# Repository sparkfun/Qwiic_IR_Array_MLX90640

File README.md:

Qwiic IR Array (MLX90640)
==================

[*Qwiic IR Array (SEN-14843)*](https://www.sparkfun.com/products/14843)
[*Qwiic IR Array (SEN-14844)*](https://www.sparkfun.com/products/14843)

The MLX90640 contains a 32x24 array of thermopile sensors creating, in essence, a low resolution thermal imaging camera.

Repository Contents
-------------------
* **/Documentation** - Datasheets. 
* **/Firmware** - Examples to use the MLX90640 with a microcontroller.
* **/Hardware** - All Eagle design files (.brd, .sch). 
* **/Production** - Various test jigs and large panel layouts used for production.

Documentation
--------------
* **[Library](https://github.com/sparkfun/SparkFun_MLX90640_Arduino_Example)** - Arduino library for the Qwiic IR Array.
* **[Hookup Guide](https://learn.sparkfun.com/tutorials/qwiic-ir-array-mlx90640-hookup-guide)** - Basic hookup guide for the Qwiic IR Array.

Product Versions
----------------
* [SEN-14843](https://www.sparkfun.com/products/14843)- SparkFun 55 degree FOV
* [SEN-14844](https://www.sparkfun.com/products/14844)- SparkFun 110 degree FOV
* [SPX-14768](https://www.sparkfun.com/products/14768)- SparkX version

License Information
-------------------

The hardware is released under [Creative Commons ShareAlike 4.0 International](https://creativecommons.org/licenses/by-sa/4.0/).
The code is beerware; if you see me (or any other SparkFun employee) at the local, and you've found our code helpful, please buy us a round!

Distributed as-is; no warranty is given.

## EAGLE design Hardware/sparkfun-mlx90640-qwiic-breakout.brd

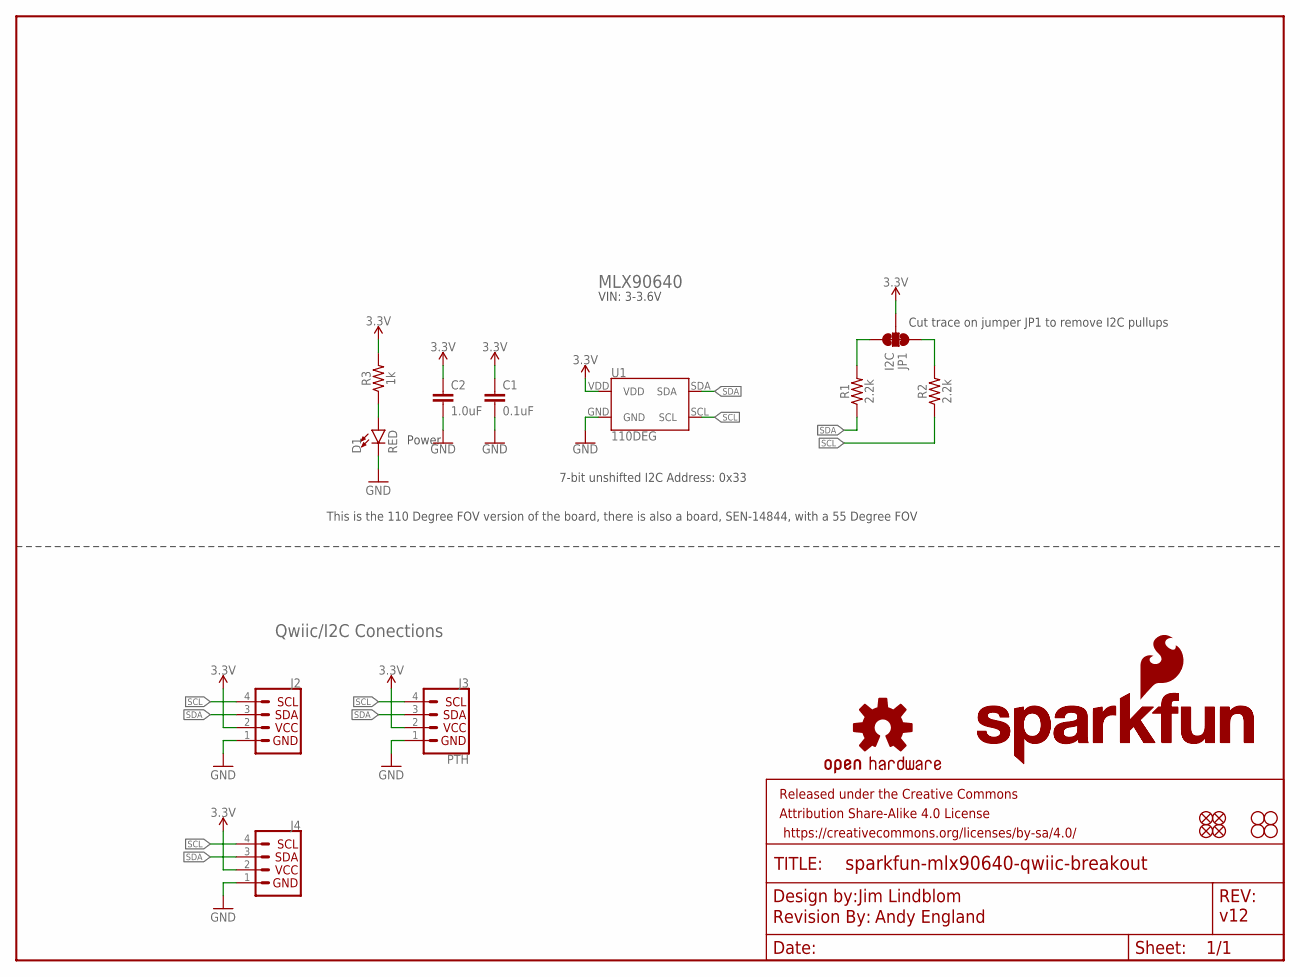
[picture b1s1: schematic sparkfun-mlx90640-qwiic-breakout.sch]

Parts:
C1: 0.1uF; 0603
C2: 1.0uF; 0603
D1: RED; LED-0603
FRAME1: FRAME-LETTER; CREATIVE_COMMONS
J2, J4: QWIIC_CONNECTORJS-1MM; JST04_1MM_RA
J3: PTH; 1X04_NO_SILK
JP1: I2C; SMT-JUMPER_3_2-NC_TRACE_NO-SILK
JP2, JP5, JP6, JP7: FIDUCIALUFIDUCIAL; MICRO-FIDUCIAL
JP3, JP4, JP8, JP9: STAND-OFF
LOGO1: OSHW-LOGOMINI; OSHW-LOGO-MINI
LOGO2: SFE_LOGO_NAME_FLAME.1_INCH; SFE_LOGO_NAME_FLAME_.1
LOGO3: SFE_LOGO_NAME.1_INCH; SFE_LOGO_NAME_.1
LOGO4: REVISION
R1, R2: 2.2k; 0603
R3: 1k; 0603
U1: 110DEG; MLX90540_MLX90640

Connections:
3.3V: C1.1, C2.1, J2.2, J3.2 (VCC), J4.2, JP1.2, R3.2, U1.VDD
GND: C1.2, C2.2, D1.C, J2.1, J3.1 (GND), J4.1, U1.GND
unnamed: JP1.3, R1.2
unnamed: JP1.1, R2.2
unnamed: D1.A, R3.1
SCL: J2.4, J3.4 (SCL), J4.4, R2.1, U1.SCL
SDA: J2.3, J3.3 (SDA), J4.3, R1.1, U1.SDA

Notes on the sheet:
Power
Jim Lindblom
7-bit unshifted I2C Address: 0x33
v12
Andy England
MLX90640
Qwiic/I2C Conections
VIN: 3-3.6V
This is the 110 Degree FOV version of the board, there is also a board, SEN-14844, with a 55 Degree FOV
Cut trace on jumper JP1 to remove I2C pullups

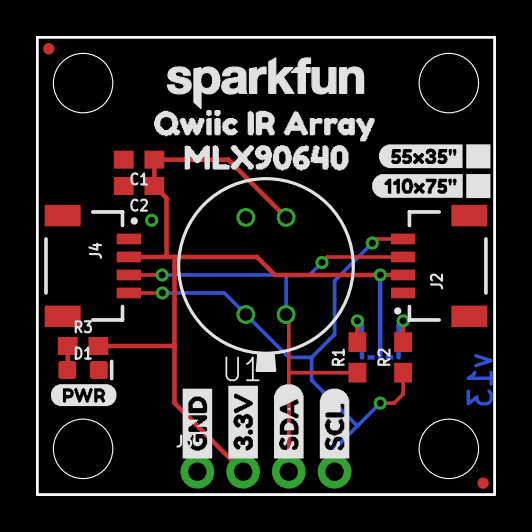
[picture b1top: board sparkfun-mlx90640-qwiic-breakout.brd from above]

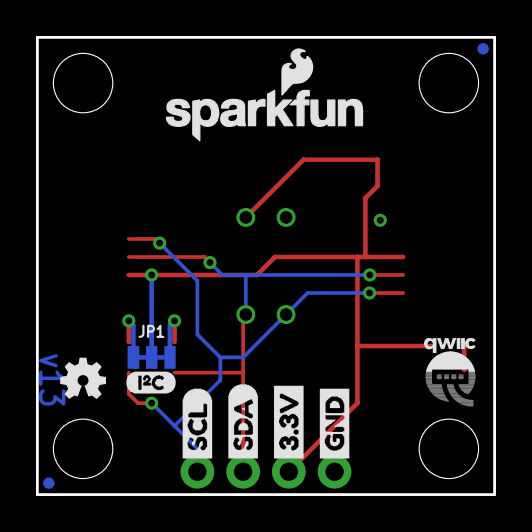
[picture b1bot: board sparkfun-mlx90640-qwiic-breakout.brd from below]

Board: 2 copper layers, 25.4 x 25.4 mm, 39 parts (11 on the bottom side), 7 nets.

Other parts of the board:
U$1, U$7: SDA-[)
U$3: 55X35#1
U$4, U$8: SCL-[)
U$5, U$9: 3.3V
U$6, U$10: GND-04
U$11: QWIIC-LOGO-SMALL
U$12: PWR-()-03
U$13: MLX906401
U$14: QWIIC_IR_ARRAY0
U$15: 110X75#0
U$16: I_SUPER2_C-()-03

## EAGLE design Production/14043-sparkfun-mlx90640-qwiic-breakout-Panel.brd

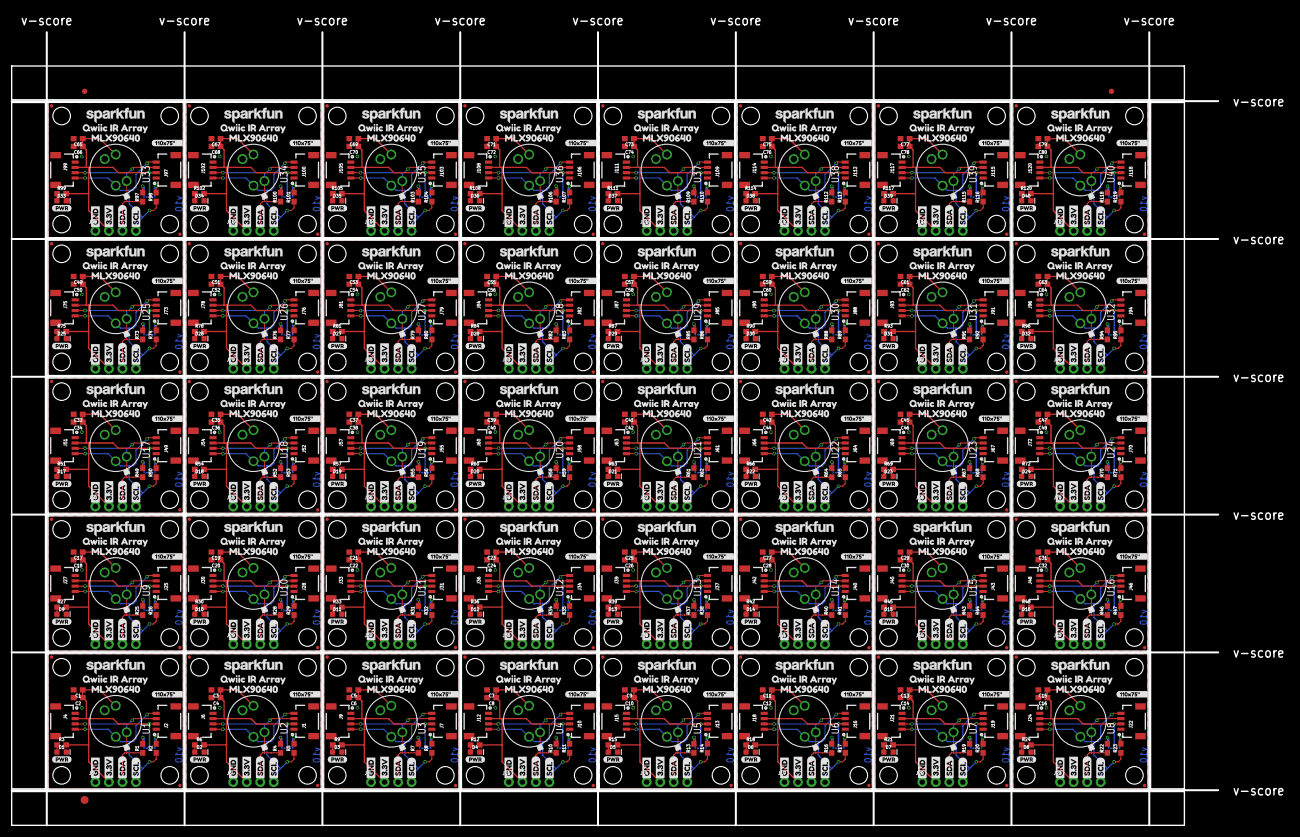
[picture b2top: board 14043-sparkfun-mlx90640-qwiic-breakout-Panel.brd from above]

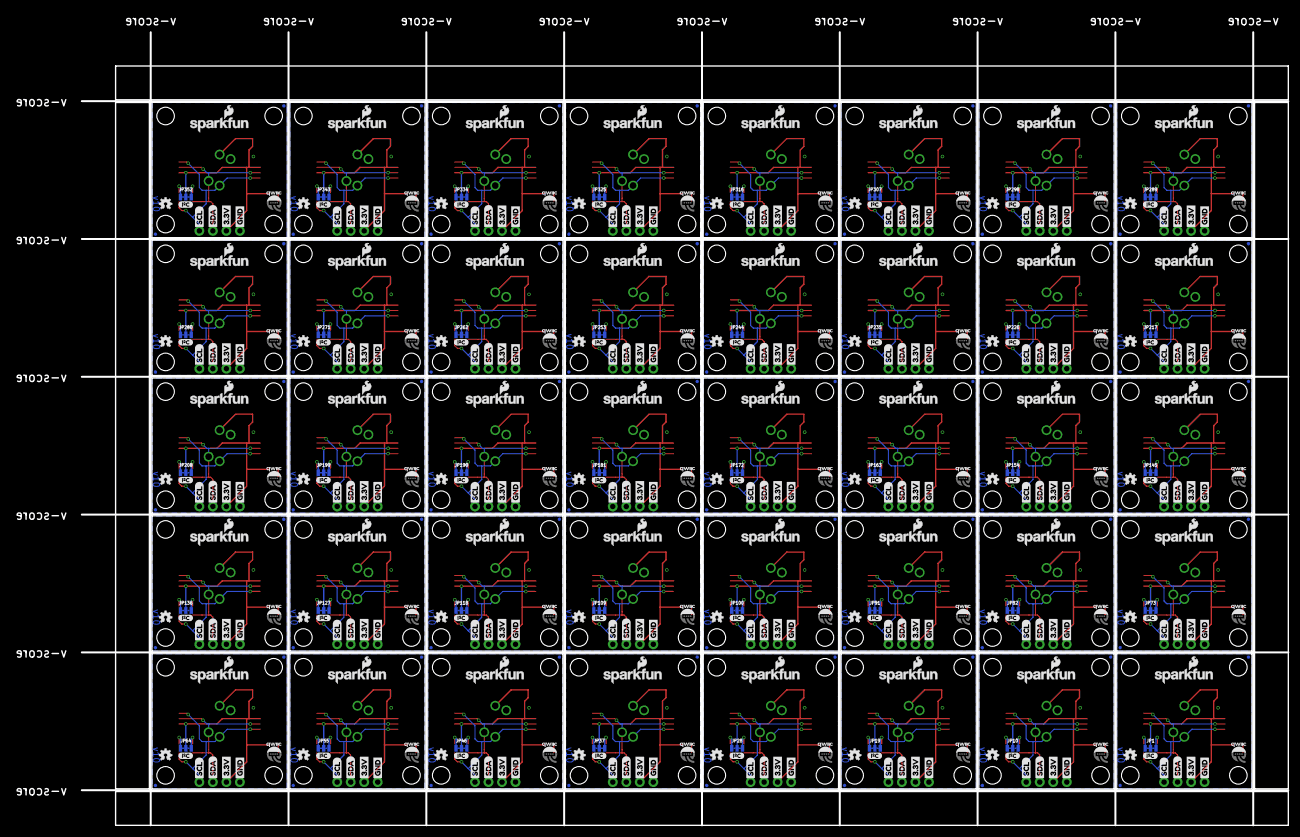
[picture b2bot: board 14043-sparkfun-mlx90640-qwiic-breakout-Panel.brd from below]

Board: 2 copper layers, 240.0 x 153.0 mm, 1443 parts (440 on the bottom side), 280 nets.

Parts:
C1, C3, C5, C7, C9, C11, C13, C15, C17, C19, C21, C23, C25, C27, C29, C31, C33, C35, C37, C39, C41, C43, C45, C47, C49, C51, C53, C55, C57, C59, C61, C63, C65, C67, C69, C71, C73, C75, C77, C79: 0.1uF; 0603
C2, C4, C6, C8, C10, C12, C14, C16, C18, C20, C22, C24, C26, C28, C30, C32, C34, C36, C38, C40, C42, C44, C46, C48, C50, C52, C54, C56, C58, C60, C62, C64, C66, C68, C70, C72, C74, C76, C78, C80: 1.0uF; 0603
D1, D2, D3, D4, D5, D6, D7, D8, D9, D10, D11, D12, D13, D14, D15, D16, D17, D18, D19, D20, D21, D22, D23, D24, D25, D26, D27, D28, D29, D30, D31, D32, D33, D34, D35, D36, D37, D38, D39, D40: RED; LED-0603
E$1, E$2: FIDUCIAL-1X2
E$3: FIDUCIAL-1.5X3
J1, J2, J4, J6, J7, J9, J10, J12, J13, J15, J16, J18, J19, J21, J22, J24, J25, J27, J28, J30, J31, J33, J34, J36, J37, J39, J40, J42, J43, J45, J46, J48, J49, J51, J52, J54, J55, J57, J58, J60, J61, J63, J64, J66, J67, J69, J70, J72, J73, J75, J76, J78, J79, J81, J82, J84, J85, J87, J88, J90, J91, J93, J94, J96, J97, J99, J100, J102, J103, J105, J106, J108, J109, J111, J112, J114, J115, J117, J118, J120: 1X04_1MM_RA
J3, J5, J8, J11, J14, J17, J20, J23, J26, J29, J32, J35, J38, J41, J44, J47, J50, J53, J56, J59, J62, J65, J68, J71, J74, J77, J80, J83, J86, J89, J92, J95, J98, J101, J104, J107, J110, J113, J116, J119: PTH; 1X04_NO_SILK
JP1, JP10, JP19, JP28, JP37, JP46, JP55, JP64, JP73, JP82, JP91, JP100, JP109, JP118, JP127, JP136, JP145, JP154, JP163, JP172, JP181, JP190, JP199, JP208, JP217, JP226, JP235, JP244, JP253, JP262, JP271, JP280, JP289, JP298, JP307, JP316, JP325, JP334, JP343, JP352: I2C; SMT-JUMPER_3_2-NC_TRACE_NO-SILK
JP2, JP5, JP6, JP7, JP13, JP14, JP15, JP16, JP22, JP23, JP24, JP25, JP31, JP32, JP33, JP34, JP40, JP41, JP42, JP43, JP49, JP50, JP51, JP52, JP58, JP59, JP60, JP61, JP67, JP68, JP69, JP70, JP76, JP77, JP78, JP79, JP85, JP86, JP87, JP88, JP94, JP95, JP96, JP97, JP103, JP104, JP105, JP106, JP112, JP113, JP114, JP115, JP121, JP122, JP123, JP124, JP130, JP131, JP132, JP133, JP139, JP140, JP141, JP142, JP148, JP149, JP150, JP151, JP157, JP158, JP159, JP160, JP166, JP167, JP168, JP169, JP175, JP176, JP177, JP178, JP184, JP185, JP186, JP187, JP193, JP194, JP195, JP196, JP202, JP203, JP204, JP205, JP211, JP212, JP213, JP214, JP220, JP221, JP222, JP223, JP229, JP230, JP231, JP232, JP238, JP239, JP240, JP241, JP247, JP248, JP249, JP250, JP256, JP257, JP258, JP259, JP265, JP266, JP267, JP268, JP274, JP275, JP276, JP277, JP283, JP284, JP285, JP286, JP292, JP293, JP294, JP295, JP301, JP302, JP303, JP304, JP310, JP311, JP312, JP313, JP319, JP320, JP321, JP322, JP328, JP329, JP330, JP331, JP337, JP338, JP339, JP340, JP346, JP347, JP348, JP349, JP355, JP356, JP357, JP358: FIDUCIALUFIDUCIAL; MICRO-FIDUCIAL
JP3, JP4, JP8, JP9, JP11, JP12, JP17, JP18, JP20, JP21, JP26, JP27, JP29, JP30, JP35, JP36, JP38, JP39, JP44, JP45, JP47, JP48, JP53, JP54, JP56, JP57, JP62, JP63, JP65, JP66, JP71, JP72, JP74, JP75, JP80, JP81, JP83, JP84, JP89, JP90, JP92, JP93, JP98, JP99, JP101, JP102, JP107, JP108, JP110, JP111, JP116, JP117, JP119, JP120, JP125, JP126, JP128, JP129, JP134, JP135, JP137, JP138, JP143, JP144, JP146, JP147, JP152, JP153, JP155, JP156, JP161, JP162, JP164, JP165, JP170, JP171, JP173, JP174, JP179, JP180, JP182, JP183, JP188, JP189, JP191, JP192, JP197, JP198, JP200, JP201, JP206, JP207, JP209, JP210, JP215, JP216, JP218, JP219, JP224, JP225, JP227, JP228, JP233, JP234, JP236, JP237, JP242, JP243, JP245, JP246, JP251, JP252, JP254, JP255, JP260, JP261, JP263, JP264, JP269, JP270, JP272, JP273, JP278, JP279, JP281, JP282, JP287, JP288, JP290, JP291, JP296, JP297, JP299, JP300, JP305, JP306, JP308, JP309, JP314, JP315, JP317, JP318, JP323, JP324, JP326, JP327, JP332, JP333, JP335, JP336, JP341, JP342, JP344, JP345, JP350, JP351, JP353, JP354, JP359, JP360: STAND-OFF
LOGO1, LOGO4, LOGO7, LOGO10, LOGO13, LOGO16, LOGO19, LOGO22, LOGO25, LOGO28, LOGO31, LOGO34, LOGO37, LOGO40, LOGO43, LOGO46, LOGO49, LOGO52, LOGO55, LOGO58, LOGO61, LOGO64, LOGO67, LOGO70, LOGO73, LOGO76, LOGO79, LOGO82, LOGO85, LOGO88, LOGO91, LOGO94, LOGO97, LOGO100, LOGO103, LOGO106, LOGO109, LOGO112, LOGO115, LOGO118: OSHW-LOGOMINI; OSHW-LOGO-MINI
LOGO2, LOGO5, LOGO8, LOGO11, LOGO14, LOGO17, LOGO20, LOGO23, LOGO26, LOGO29, LOGO32, LOGO35, LOGO38, LOGO41, LOGO44, LOGO47, LOGO50, LOGO53, LOGO56, LOGO59, LOGO62, LOGO65, LOGO68, LOGO71, LOGO74, LOGO77, LOGO80, LOGO83, LOGO86, LOGO89, LOGO92, LOGO95, LOGO98, LOGO101, LOGO104, LOGO107, LOGO110, LOGO113, LOGO116, LOGO119: SFE_LOGO_NAME_FLAME.1_INCH; SFE_LOGO_NAME_FLAME_.1
LOGO3, LOGO6, LOGO9, LOGO12, LOGO15, LOGO18, LOGO21, LOGO24, LOGO27, LOGO30, LOGO33, LOGO36, LOGO39, LOGO42, LOGO45, LOGO48, LOGO51, LOGO54, LOGO57, LOGO60, LOGO63, LOGO66, LOGO69, LOGO72, LOGO75, LOGO78, LOGO81, LOGO84, LOGO87, LOGO90, LOGO93, LOGO96, LOGO99, LOGO102, LOGO105, LOGO108, LOGO111, LOGO114, LOGO117, LOGO120: SFE_LOGO_NAME.1_INCH; SFE_LOGO_NAME_.1
R1, R2, R4, R5, R7, R8, R10, R11, R13, R14, R16, R17, R19, R20, R22, R23, R25, R26, R28, R29, R31, R32, R34, R35, R37, R38, R40, R41, R43, R44, R46, R47, R49, R50, R52, R53, R55, R56, R58, R59, R61, R62, R64, R65, R67, R68, R70, R71, R73, R74, R76, R77, R79, R80, R82, R83, R85, R86, R88, R89, R91, R92, R94, R95, R97, R98, R100, R101, R103, R104, R106, R107, R109, R110, R112, R113, R115, R116, R118, R119: 2.2k; 0603
R3, R6, R9, R12, R15, R18, R21, R24, R27, R30, R33, R36, R39, R42, R45, R48, R51, R54, R57, R60, R63, R66, R69, R72, R75, R78, R81, R84, R87, R90, R93, R96, R99, R102, R105, R108, R111, R114, R117, R120: 1k; 0603
U1, U2, U3, U4, U5, U6, U7, U8, U9, U10, U11, U12, U13, U14, U15, U16, U17, U18, U19, U20, U21, U22, U23, U24, U25, U26, U27, U28, U29, U30, U31, U32, U33, U34, U35, U36, U37, U38, U39, U40: 110DEG; MLX90540_MLX90640
U$1, U$3, U$7, U$19, U$29, U$33, U$43, U$47, U$57, U$61, U$71, U$75, U$85, U$89, U$99, U$103, U$113, U$117, U$127, U$131, U$141, U$145, U$155, U$159, U$169, U$173, U$183, U$187, U$197, U$201, U$211, U$215, U$225, U$229, U$239, U$243, U$253, U$257, U$267, U$271, U$281, U$285, U$295, U$299, U$309, U$313, U$323, U$327, U$337, U$341, U$351, U$355, U$365, U$369, U$379, U$383, U$393, U$397, U$407, U$411, U$421, U$425, U$435, U$439, U$449, U$453, U$463, U$467, U$477, U$481, U$491, U$495, U$505, U$509, U$519, U$523, U$533, U$537, U$547, U$551: SDA-[)
U$2, U$28, U$42, U$56, U$70, U$84, U$98, U$112, U$126, U$140, U$154, U$168, U$182, U$196, U$210, U$224, U$238, U$252, U$266, U$280, U$294, U$308, U$322, U$336, U$350, U$364, U$378, U$392, U$406, U$420, U$434, U$448, U$462, U$476, U$490, U$504, U$518, U$532, U$546, U$560: 110X75#____0
U$4, U$8, U$15, U$20, U$30, U$34, U$44, U$48, U$58, U$62, U$72, U$76, U$86, U$90, U$100, U$104, U$114, U$118, U$128, U$132, U$142, U$146, U$156, U$160, U$170, U$174, U$184, U$188, U$198, U$202, U$212, U$216, U$226, U$230, U$240, U$244, U$254, U$258, U$268, U$272, U$282, U$286, U$296, U$300, U$310, U$314, U$324, U$328, U$338, U$342, U$352, U$356, U$366, U$370, U$380, U$384, U$394, U$398, U$408, U$412, U$422, U$426, U$436, U$440, U$450, U$454, U$464, U$468, U$478, U$482, U$492, U$496, U$506, U$510, U$520, U$524, U$534, U$538, U$548, U$552: SCL-[)
U$5, U$9, U$17, U$21, U$31, U$35, U$45, U$49, U$59, U$63, U$73, U$77, U$87, U$91, U$101, U$105, U$115, U$119, U$129, U$133, U$143, U$147, U$157, U$161, U$171, U$175, U$185, U$189, U$199, U$203, U$213, U$217, U$227, U$231, U$241, U$245, U$255, U$259, U$269, U$273, U$283, U$287, U$297, U$301, U$311, U$315, U$325, U$329, U$339, U$343, U$353, U$357, U$367, U$371, U$381, U$385, U$395, U$399, U$409, U$413, U$423, U$427, U$437, U$441, U$451, U$455, U$465, U$469, U$479, U$483, U$493, U$497, U$507, U$511, U$521, U$525, U$535, U$539, U$549, U$553: 3.3V
U$6, U$10, U$18, U$22, U$32, U$36, U$46, U$50, U$60, U$64, U$74, U$78, U$88, U$92, U$102, U$106, U$116, U$120, U$130, U$134, U$144, U$148, U$158, U$162, U$172, U$176, U$186, U$190, U$200, U$204, U$214, U$218, U$228, U$232, U$242, U$246, U$256, U$260, U$270, U$274, U$284, U$288, U$298, U$302, U$312, U$316, U$326, U$330, U$340, U$344, U$354, U$358, U$368, U$372, U$382, U$386, U$396, U$400, U$410, U$414, U$424, U$428, U$438, U$442, U$452, U$456, U$466, U$470, U$480, U$484, U$494, U$498, U$508, U$512, U$522, U$526, U$536, U$540, U$550, U$554: GND-04
U$11, U$23, U$37, U$51, U$65, U$79, U$93, U$107, U$121, U$135, U$149, U$163, U$177, U$191, U$205, U$219, U$233, U$247, U$261, U$275, U$289, U$303, U$317, U$331, U$345, U$359, U$373, U$387, U$401, U$415, U$429, U$443, U$457, U$471, U$485, U$499, U$513, U$527, U$541, U$555: QWIIC-LOGO-SMALL
U$12, U$24, U$38, U$52, U$66, U$80, U$94, U$108, U$122, U$136, U$150, U$164, U$178, U$192, U$206, U$220, U$234, U$248, U$262, U$276, U$290, U$304, U$318, U$332, U$346, U$360, U$374, U$388, U$402, U$416, U$430, U$444, U$458, U$472, U$486, U$500, U$514, U$528, U$542, U$556: PWR-()-03
U$13, U$25, U$39, U$53, U$67, U$81, U$95, U$109, U$123, U$137, U$151, U$165, U$179, U$193, U$207, U$221, U$235, U$249, U$263, U$277, U$291, U$305, U$319, U$333, U$347, U$361, U$375, U$389, U$403, U$417, U$431, U$445, U$459, U$473, U$487, U$501, U$515, U$529, U$543, U$557: MLX906401
U$14, U$26, U$40, U$54, U$68, U$82, U$96, U$110, U$124, U$138, U$152, U$166, U$180, U$194, U$208, U$222, U$236, U$250, U$264, U$278, U$292, U$306, U$320, U$334, U$348, U$362, U$376, U$390, U$404, U$418, U$432, U$446, U$460, U$474, U$488, U$502, U$516, U$530, U$544, U$558: QWIIC_IR_ARRAY0
U$16, U$27, U$41, U$55, U$69, U$83, U$97, U$111, U$125, U$139, U$153, U$167, U$181, U$195, U$209, U$223, U$237, U$251, U$265, U$279, U$293, U$307, U$321, U$335, U$349, U$363, U$377, U$391, U$405, U$419, U$433, U$447, U$461, U$475, U$489, U$503, U$517, U$531, U$545, U$559: I_SUPER2_C-()-03

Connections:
3.3V: C1.1, C2.1, J2.2, J3.2, J4.2, JP1.2, R3.2, U1.VDD
3.3V1: C3.1, C4.1, J1.2, J5.2, J6.2, JP10.2, R6.2, U2.VDD
3.3V2: C5.1, C6.1, J7.2, J8.2, J9.2, JP19.2, R9.2, U3.VDD
3.3V3: C7.1, C8.1, J10.2, J11.2, J12.2, JP28.2, R12.2, U4.VDD
3.3V4: C9.1, C10.1, J13.2, J14.2, J15.2, JP37.2, R15.2, U5.VDD
3.3V5: C11.1, C12.1, J16.2, J17.2, J18.2, JP46.2, R18.2, U6.VDD
3.3V6: C13.1, C14.1, J19.2, J20.2, J21.2, JP55.2, R21.2, U7.VDD
3.3V7: C15.1, C16.1, J22.2, J23.2, J24.2, JP64.2, R24.2, U8.VDD
3.3V8: C17.1, C18.1, J25.2, J26.2, J27.2, JP73.2, R27.2, U9.VDD
3.3V9: C19.1, C20.1, J28.2, J29.2, J30.2, JP82.2, R30.2, U10.VDD
3.3V10: C21.1, C22.1, J31.2, J32.2, J33.2, JP91.2, R33.2, U11.VDD
3.3V11: C23.1, C24.1, J34.2, J35.2, J36.2, JP100.2, R36.2, U12.VDD
3.3V12: C25.1, C26.1, J37.2, J38.2, J39.2, JP109.2, R39.2, U13.VDD
3.3V13: C27.1, C28.1, J40.2, J41.2, J42.2, JP118.2, R42.2, U14.VDD
3.3V14: C29.1, C30.1, J43.2, J44.2, J45.2, JP127.2, R45.2, U15.VDD
3.3V15: C31.1, C32.1, J46.2, J47.2, J48.2, JP136.2, R48.2, U16.VDD
3.3V16: C33.1, C34.1, J49.2, J50.2, J51.2, JP145.2, R51.2, U17.VDD
3.3V17: C35.1, C36.1, J52.2, J53.2, J54.2, JP154.2, R54.2, U18.VDD
3.3V18: C37.1, C38.1, J55.2, J56.2, J57.2, JP163.2, R57.2, U19.VDD
3.3V19: C39.1, C40.1, J58.2, J59.2, J60.2, JP172.2, R60.2, U20.VDD
3.3V20: C41.1, C42.1, J61.2, J62.2, J63.2, JP181.2, R63.2, U21.VDD
3.3V21: C43.1, C44.1, J64.2, J65.2, J66.2, JP190.2, R66.2, U22.VDD
3.3V22: C45.1, C46.1, J67.2, J68.2, J69.2, JP199.2, R69.2, U23.VDD
3.3V23: C47.1, C48.1, J70.2, J71.2, J72.2, JP208.2, R72.2, U24.VDD
3.3V24: C49.1, C50.1, J73.2, J74.2, J75.2, JP217.2, R75.2, U25.VDD
3.3V25: C51.1, C52.1, J76.2, J77.2, J78.2, JP226.2, R78.2, U26.VDD
3.3V26: C53.1, C54.1, J79.2, J80.2, J81.2, JP235.2, R81.2, U27.VDD
3.3V27: C55.1, C56.1, J82.2, J83.2, J84.2, JP244.2, R84.2, U28.VDD
3.3V28: C57.1, C58.1, J85.2, J86.2, J87.2, JP253.2, R87.2, U29.VDD
3.3V29: C59.1, C60.1, J88.2, J89.2, J90.2, JP262.2, R90.2, U30.VDD
3.3V30: C61.1, C62.1, J91.2, J92.2, J93.2, JP271.2, R93.2, U31.VDD
3.3V31: C63.1, C64.1, J94.2, J95.2, J96.2, JP280.2, R96.2, U32.VDD
3.3V32: C65.1, C66.1, J97.2, J98.2, J99.2, JP289.2, R99.2, U33.VDD
3.3V33: C67.1, C68.1, J100.2, J101.2, J102.2, JP298.2, R102.2, U34.VDD
3.3V34: C69.1, C70.1, J103.2, J104.2, J105.2, JP307.2, R105.2, U35.VDD
3.3V35: C71.1, C72.1, J106.2, J107.2, J108.2, JP316.2, R108.2, U36.VDD
3.3V36: C73.1, C74.1, J109.2, J110.2, J111.2, JP325.2, R111.2, U37.VDD
3.3V37: C75.1, C76.1, J112.2, J113.2, J114.2, JP334.2, R114.2, U38.VDD
3.3V38: C77.1, C78.1, J115.2, J116.2, J117.2, JP343.2, R117.2, U39.VDD
3.3V39: C79.1, C80.1, J118.2, J119.2, J120.2, JP352.2, R120.2, U40.VDD
GND: C1.2, C2.2, D1.C, J2.1, J3.1, J4.1, U1.GND
GND1: C3.2, C4.2, D2.C, J1.1, J5.1, J6.1, U2.GND
GND2: C5.2, C6.2, D3.C, J7.1, J8.1, J9.1, U3.GND
GND3: C7.2, C8.2, D4.C, J10.1, J11.1, J12.1, U4.GND
GND4: C9.2, C10.2, D5.C, J13.1, J14.1, J15.1, U5.GND
GND5: C11.2, C12.2, D6.C, J16.1, J17.1, J18.1, U6.GND
GND6: C13.2, C14.2, D7.C, J19.1, J20.1, J21.1, U7.GND
GND7: C15.2, C16.2, D8.C, J22.1, J23.1, J24.1, U8.GND
GND8: C17.2, C18.2, D9.C, J25.1, J26.1, J27.1, U9.GND
GND9: C19.2, C20.2, D10.C, J28.1, J29.1, J30.1, U10.GND
GND10: C21.2, C22.2, D11.C, J31.1, J32.1, J33.1, U11.GND
GND11: C23.2, C24.2, D12.C, J34.1, J35.1, J36.1, U12.GND
GND12: C25.2, C26.2, D13.C, J37.1, J38.1, J39.1, U13.GND
GND13: C27.2, C28.2, D14.C, J40.1, J41.1, J42.1, U14.GND
GND14: C29.2, C30.2, D15.C, J43.1, J44.1, J45.1, U15.GND
GND15: C31.2, C32.2, D16.C, J46.1, J47.1, J48.1, U16.GND
GND16: C33.2, C34.2, D17.C, J49.1, J50.1, J51.1, U17.GND
GND17: C35.2, C36.2, D18.C, J52.1, J53.1, J54.1, U18.GND
GND18: C37.2, C38.2, D19.C, J55.1, J56.1, J57.1, U19.GND
GND19: C39.2, C40.2, D20.C, J58.1, J59.1, J60.1, U20.GND
GND20: C41.2, C42.2, D21.C, J61.1, J62.1, J63.1, U21.GND
GND21: C43.2, C44.2, D22.C, J64.1, J65.1, J66.1, U22.GND
GND22: C45.2, C46.2, D23.C, J67.1, J68.1, J69.1, U23.GND
GND23: C47.2, C48.2, D24.C, J70.1, J71.1, J72.1, U24.GND
GND24: C49.2, C50.2, D25.C, J73.1, J74.1, J75.1, U25.GND
GND25: C51.2, C52.2, D26.C, J76.1, J77.1, J78.1, U26.GND
GND26: C53.2, C54.2, D27.C, J79.1, J80.1, J81.1, U27.GND
GND27: C55.2, C56.2, D28.C, J82.1, J83.1, J84.1, U28.GND
GND28: C57.2, C58.2, D29.C, J85.1, J86.1, J87.1, U29.GND
GND29: C59.2, C60.2, D30.C, J88.1, J89.1, J90.1, U30.GND
GND30: C61.2, C62.2, D31.C, J91.1, J92.1, J93.1, U31.GND
GND31: C63.2, C64.2, D32.C, J94.1, J95.1, J96.1, U32.GND
GND32: C65.2, C66.2, D33.C, J97.1, J98.1, J99.1, U33.GND
GND33: C67.2, C68.2, D34.C, J100.1, J101.1, J102.1, U34.GND
GND34: C69.2, C70.2, D35.C, J103.1, J104.1, J105.1, U35.GND
GND35: C71.2, C72.2, D36.C, J106.1, J107.1, J108.1, U36.GND
GND36: C73.2, C74.2, D37.C, J109.1, J110.1, J111.1, U37.GND
GND37: C75.2, C76.2, D38.C, J112.1, J113.1, J114.1, U38.GND
GND38: C77.2, C78.2, D39.C, J115.1, J116.1, J117.1, U39.GND
GND39: C79.2, C80.2, D40.C, J118.1, J119.1, J120.1, U40.GND
unnamed: JP1.3, R1.2
unnamed: JP1.1, R2.2
unnamed: D1.A, R3.1
unnamed: JP10.3, R4.2
unnamed: JP10.1, R5.2
unnamed: D2.A, R6.1
unnamed: JP19.3, R7.2
unnamed: JP19.1, R8.2
unnamed: D3.A, R9.1
unnamed: JP28.3, R10.2
unnamed: JP28.1, R11.2
unnamed: D4.A, R12.1
unnamed: JP37.3, R13.2
unnamed: JP37.1, R14.2
unnamed: D5.A, R15.1
unnamed: JP46.3, R16.2
unnamed: JP46.1, R17.2
unnamed: D6.A, R18.1
unnamed: JP55.3, R19.2
unnamed: JP55.1, R20.2
unnamed: D7.A, R21.1
unnamed: JP64.3, R22.2
unnamed: JP64.1, R23.2
unnamed: D8.A, R24.1
unnamed: JP73.3, R25.2
unnamed: JP73.1, R26.2
unnamed: D9.A, R27.1
unnamed: JP82.3, R28.2
unnamed: JP82.1, R29.2
unnamed: D10.A, R30.1
unnamed: JP91.3, R31.2
unnamed: JP91.1, R32.2
unnamed: D11.A, R33.1
unnamed: JP100.3, R34.2
unnamed: JP100.1, R35.2
unnamed: D12.A, R36.1
unnamed: JP109.3, R37.2
unnamed: JP109.1, R38.2
unnamed: D13.A, R39.1
unnamed: JP118.3, R40.2
unnamed: JP118.1, R41.2
unnamed: D14.A, R42.1
unnamed: JP127.3, R43.2
unnamed: JP127.1, R44.2
unnamed: D15.A, R45.1
unnamed: JP136.3, R46.2
unnamed: JP136.1, R47.2
unnamed: D16.A, R48.1
unnamed: JP145.3, R49.2
unnamed: JP145.1, R50.2
unnamed: D17.A, R51.1
unnamed: JP154.3, R52.2
unnamed: JP154.1, R53.2
unnamed: D18.A, R54.1
unnamed: JP163.3, R55.2
unnamed: JP163.1, R56.2
unnamed: D19.A, R57.1
unnamed: JP172.3, R58.2
unnamed: JP172.1, R59.2
unnamed: D20.A, R60.1
unnamed: JP181.3, R61.2
unnamed: JP181.1, R62.2
unnamed: D21.A, R63.1
unnamed: JP190.3, R64.2
unnamed: JP190.1, R65.2
unnamed: D22.A, R66.1
unnamed: JP199.3, R67.2
unnamed: JP199.1, R68.2
unnamed: D23.A, R69.1
unnamed: JP208.3, R70.2
unnamed: JP208.1, R71.2
unnamed: D24.A, R72.1
unnamed: JP217.3, R73.2
unnamed: JP217.1, R74.2
unnamed: D25.A, R75.1
unnamed: JP226.3, R76.2
unnamed: JP226.1, R77.2
unnamed: D26.A, R78.1
unnamed: JP235.3, R79.2
unnamed: JP235.1, R80.2
unnamed: D27.A, R81.1
unnamed: JP244.3, R82.2
unnamed: JP244.1, R83.2
unnamed: D28.A, R84.1
unnamed: JP253.3, R85.2
unnamed: JP253.1, R86.2
unnamed: D29.A, R87.1
unnamed: JP262.3, R88.2
unnamed: JP262.1, R89.2
unnamed: D30.A, R90.1
unnamed: JP271.3, R91.2
unnamed: JP271.1, R92.2
unnamed: D31.A, R93.1
unnamed: JP280.3, R94.2
unnamed: JP280.1, R95.2
unnamed: D32.A, R96.1
unnamed: JP289.3, R97.2
unnamed: JP289.1, R98.2
unnamed: D33.A, R99.1
unnamed: JP298.3, R100.2
unnamed: JP298.1, R101.2
unnamed: D34.A, R102.1
unnamed: JP307.3, R103.2
unnamed: JP307.1, R104.2
unnamed: D35.A, R105.1
unnamed: JP316.3, R106.2
unnamed: JP316.1, R107.2
unnamed: D36.A, R108.1
unnamed: JP325.3, R109.2
unnamed: JP325.1, R110.2
unnamed: D37.A, R111.1
unnamed: JP334.3, R112.2
unnamed: JP334.1, R113.2
unnamed: D38.A, R114.1
unnamed: JP343.3, R115.2
unnamed: JP343.1, R116.2
unnamed: D39.A, R117.1
unnamed: JP352.3, R118.2
unnamed: JP352.1, R119.2
unnamed: D40.A, R120.1
SCL: J2.4, J3.4, J4.4, R2.1, U1.SCL
SCL1: J1.4, J5.4, J6.4, R5.1, U2.SCL
SCL2: J7.4, J8.4, J9.4, R8.1, U3.SCL
SCL3: J10.4, J11.4, J12.4, R11.1, U4.SCL
SCL4: J13.4, J14.4, J15.4, R14.1, U5.SCL
SCL5: J16.4, J17.4, J18.4, R17.1, U6.SCL
SCL6: J19.4, J20.4, J21.4, R20.1, U7.SCL
SCL7: J22.4, J23.4, J24.4, R23.1, U8.SCL
SCL8: J25.4, J26.4, J27.4, R26.1, U9.SCL
SCL9: J28.4, J29.4, J30.4, R29.1, U10.SCL
SCL10: J31.4, J32.4, J33.4, R32.1, U11.SCL
SCL11: J34.4, J35.4, J36.4, R35.1, U12.SCL
SCL12: J37.4, J38.4, J39.4, R38.1, U13.SCL
SCL13: J40.4, J41.4, J42.4, R41.1, U14.SCL
SCL14: J43.4, J44.4, J45.4, R44.1, U15.SCL
SCL15: J46.4, J47.4, J48.4, R47.1, U16.SCL
SCL16: J49.4, J50.4, J51.4, R50.1, U17.SCL
SCL17: J52.4, J53.4, J54.4, R53.1, U18.SCL
SCL18: J55.4, J56.4, J57.4, R56.1, U19.SCL
SCL19: J58.4, J59.4, J60.4, R59.1, U20.SCL
SCL20: J61.4, J62.4, J63.4, R62.1, U21.SCL
SCL21: J64.4, J65.4, J66.4, R65.1, U22.SCL
SCL22: J67.4, J68.4, J69.4, R68.1, U23.SCL
SCL23: J70.4, J71.4, J72.4, R71.1, U24.SCL
SCL24: J73.4, J74.4, J75.4, R74.1, U25.SCL
SCL25: J76.4, J77.4, J78.4, R77.1, U26.SCL
SCL26: J79.4, J80.4, J81.4, R80.1, U27.SCL
SCL27: J82.4, J83.4, J84.4, R83.1, U28.SCL
SCL28: J85.4, J86.4, J87.4, R86.1, U29.SCL
SCL29: J88.4, J89.4, J90.4, R89.1, U30.SCL
SCL30: J91.4, J92.4, J93.4, R92.1, U31.SCL
SCL31: J94.4, J95.4, J96.4, R95.1, U32.SCL
SCL32: J97.4, J98.4, J99.4, R98.1, U33.SCL
SCL33: J100.4, J101.4, J102.4, R101.1, U34.SCL
SCL34: J103.4, J104.4, J105.4, R104.1, U35.SCL
SCL35: J106.4, J107.4, J108.4, R107.1, U36.SCL
SCL36: J109.4, J110.4, J111.4, R110.1, U37.SCL
SCL37: J112.4, J113.4, J114.4, R113.1, U38.SCL
SCL38: J115.4, J116.4, J117.4, R116.1, U39.SCL
SCL39: J118.4, J119.4, J120.4, R119.1, U40.SCL
SDA: J2.3, J3.3, J4.3, R1.1, U1.SDA
SDA1: J1.3, J5.3, J6.3, R4.1, U2.SDA
SDA2: J7.3, J8.3, J9.3, R7.1, U3.SDA
SDA3: J10.3, J11.3, J12.3, R10.1, U4.SDA
SDA4: J13.3, J14.3, J15.3, R13.1, U5.SDA
SDA5: J16.3, J17.3, J18.3, R16.1, U6.SDA
SDA6: J19.3, J20.3, J21.3, R19.1, U7.SDA
SDA7: J22.3, J23.3, J24.3, R22.1, U8.SDA
SDA8: J25.3, J26.3, J27.3, R25.1, U9.SDA
SDA9: J28.3, J29.3, J30.3, R28.1, U10.SDA
SDA10: J31.3, J32.3, J33.3, R31.1, U11.SDA
SDA11: J34.3, J35.3, J36.3, R34.1, U12.SDA
SDA12: J37.3, J38.3, J39.3, R37.1, U13.SDA
SDA13: J40.3, J41.3, J42.3, R40.1, U14.SDA
SDA14: J43.3, J44.3, J45.3, R43.1, U15.SDA
SDA15: J46.3, J47.3, J48.3, R46.1, U16.SDA
SDA16: J49.3, J50.3, J51.3, R49.1, U17.SDA
SDA17: J52.3, J53.3, J54.3, R52.1, U18.SDA
SDA18: J55.3, J56.3, J57.3, R55.1, U19.SDA
SDA19: J58.3, J59.3, J60.3, R58.1, U20.SDA
SDA20: J61.3, J62.3, J63.3, R61.1, U21.SDA
SDA21: J64.3, J65.3, J66.3, R64.1, U22.SDA
SDA22: J67.3, J68.3, J69.3, R67.1, U23.SDA
SDA23: J70.3, J71.3, J72.3, R70.1, U24.SDA
SDA24: J73.3, J74.3, J75.3, R73.1, U25.SDA
SDA25: J76.3, J77.3, J78.3, R76.1, U26.SDA
SDA26: J79.3, J80.3, J81.3, R79.1, U27.SDA
SDA27: J82.3, J83.3, J84.3, R82.1, U28.SDA
SDA28: J85.3, J86.3, J87.3, R85.1, U29.SDA
SDA29: J88.3, J89.3, J90.3, R88.1, U30.SDA
SDA30: J91.3, J92.3, J93.3, R91.1, U31.SDA
SDA31: J94.3, J95.3, J96.3, R94.1, U32.SDA
SDA32: J97.3, J98.3, J99.3, R97.1, U33.SDA
SDA33: J100.3, J101.3, J102.3, R100.1, U34.SDA
SDA34: J103.3, J104.3, J105.3, R103.1, U35.SDA
SDA35: J106.3, J107.3, J108.3, R106.1, U36.SDA
SDA36: J109.3, J110.3, J111.3, R109.1, U37.SDA
SDA37: J112.3, J113.3, J114.3, R112.1, U38.SDA
SDA38: J115.3, J116.3, J117.3, R115.1, U39.SDA
SDA39: J118.3, J119.3, J120.3, R118.1, U40.SDA

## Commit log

2018-07-10 updating to reds
2018-07-17 Post design review changes
2018-07-30 fixing issues
2018-08-03 panel v10 created
2018-09-18 updating to kit package
2018-09-20 cleaning repo
2018-09-20 updating readme
2018-11-19 fixing orientation
2018-11-21 Updating silk for single PCB design
2018-11-28 panel
2019-09-30 pulling in PTH holes, needs repanel

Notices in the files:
parts and their libraries:
SparkFun-Capacitors: Licensing: Creative Commons ShareAlike 4.0 International - https://creativecommons.org/licenses/by-sa/4.0
SparkFun-Aesthetics: Released under the Creative Commons Attribution Share-Alike 4.0 License
SparkFun-Aesthetics: Released under the Creative Commons
